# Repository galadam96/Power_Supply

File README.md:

# Power_Supply
KiCAD based project for a simple BreadBoard Power Supply based on KiCad Like a Pro, 3rd Edition By Dr Peter Dalmaris

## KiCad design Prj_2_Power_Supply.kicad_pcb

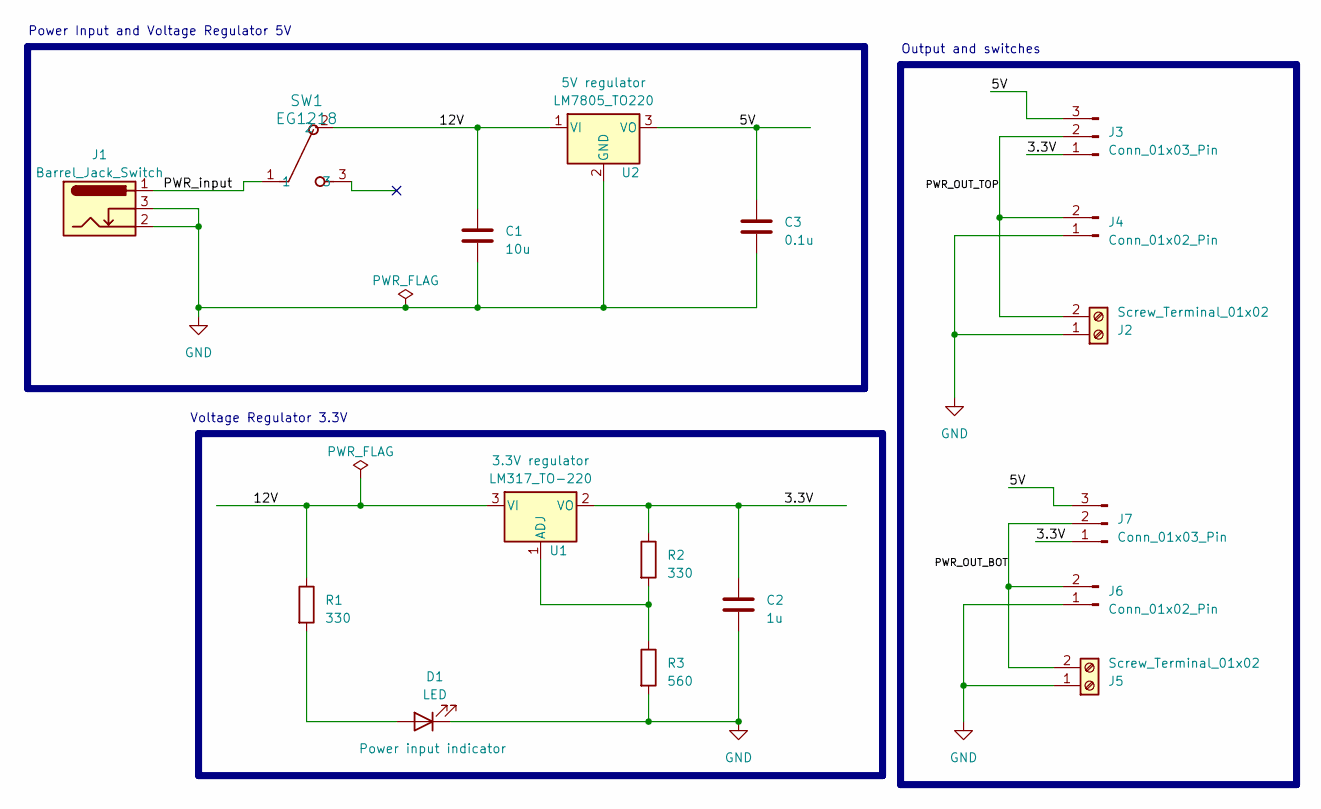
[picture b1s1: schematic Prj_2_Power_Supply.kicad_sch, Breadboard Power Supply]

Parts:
C1: 10u; C_Disc_D3.0mm_W1.6mm_P2.50mm
C2: 1u; C_Disc_D3.0mm_W1.6mm_P2.50mm
C3: 0.1u; C_Disc_D3.0mm_W1.6mm_P2.50mm
D1: LED; LED_D5.0mm
J1: Barrel_Jack_Switch; BarrelJack_Horizontal
J2, J5: Screw_Terminal_01x02; TerminalBlock_bornier-2_P5.08mm
J3, J7: Conn_01x03_Pin; PinHeader_1x03_P2.54mm_Vertical
J4, J6: Conn_01x02_Pin; PinHeader_1x02_P2.54mm_Vertical
R1, R2: 330; R_Axial_DIN0204_L3.6mm_D1.6mm_P7.62mm_Horizontal
R3: 560; R_Axial_DIN0204_L3.6mm_D1.6mm_P7.62mm_Horizontal
SW1: EG1218
U1: LM317_TO-220; TO-220-3_Vertical
U2: LM7805_TO220; TO-220-3_Vertical

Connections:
/3.3V: C2.1, J3.1, J7.1, R2.1, U1.2 (VO)
/5V: C3.1, J3.3, J7.3, U2.3 (VO)
/12V: C1.1, R1.1, SW1.2, U1.3 (VI), U2.1 (VI)
/PWR_OUT_BOT: J5.2, J6.2, J7.2
/PWR_OUT_TOP: J2.2, J3.2, J4.2
/PWR_input: J1.1, SW1.1
GND: C1.2, C2.2, C3.2, D1.1 (K), J1.2, J1.3, J2.1, J4.1, J5.1, J6.1, R3.2, U2.2 (GND)
unnamed: D1.2 (A), R1.2
unnamed: R2.2, R3.1, U1.1 (ADJ)

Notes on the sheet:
Power Input and Voltage Regulator 5V
Output and switches
Voltage Regulator 3.3V

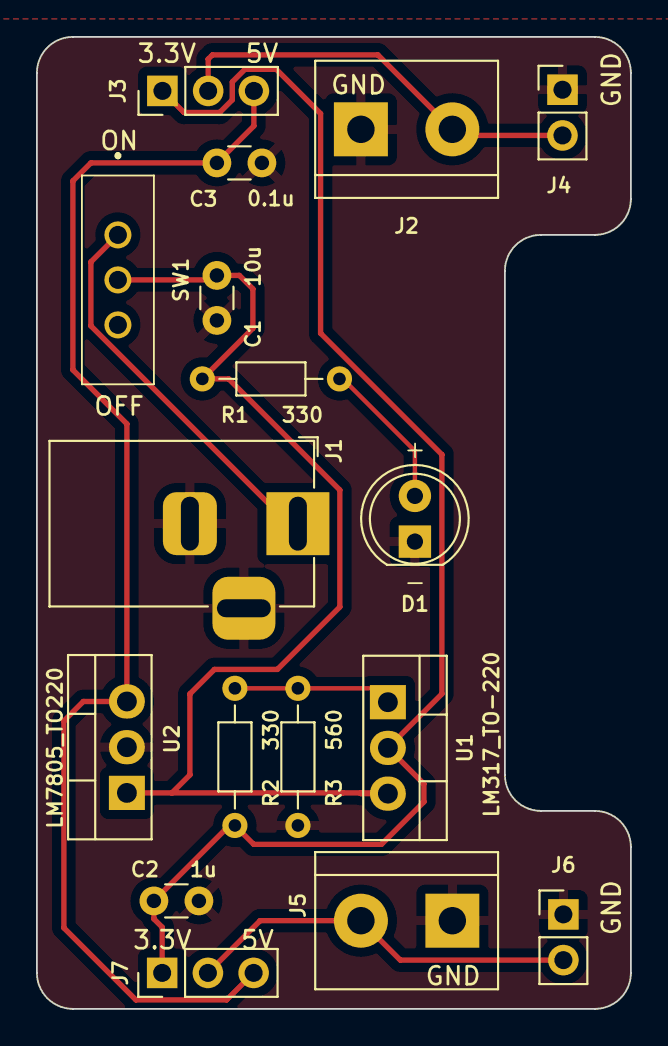
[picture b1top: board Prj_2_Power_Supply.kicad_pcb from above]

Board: 2 copper layers, 33.0 x 54.0 mm, 17 parts (0 on the bottom side), 9 nets.

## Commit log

2023-05-01 Files uploaded
